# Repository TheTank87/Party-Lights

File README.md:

# Tropical-Fruit-Bowl

# Description
A custom designed PCB that can track humidity, temperature, air pressure, and air quality in ppm. It also includes a gyrscope sensor. This project was heavily inspired by the Starbie and MIDI keyboard projects I did previously, and I wanted to combine them with some new components to see what I can make. This was a pretty exciting experience for me, because for once, I'm not following a guide anymore, and with the lessons and techniques I learned from the previous projects it's like building with LEGO. Once something becomes as fluent as LEGO building, I can let creativity take over.

# Features
* DHT11 Sensor
* MPU6050 gyro Sensor
* The new ENS160+AHT21 air quality sensor
* 2 low profile switches
* Potentiometer
* Rotary Encoder
* OLED

# BOM
| Item | Qty | Supplier | Cost/item | Total Cost | Link |
| --- | --- | --- | --- | --- | --- |
| 0.96 OLED | 1 | AliExpress | $4.38 | $4.38 | [Link](https://www.aliexpress.us/item/3256807427834365.html?src=google&src=google&albch=shopping&acnt=708-803-3821&isdl=y&slnk=&plac=&mtctp=&albbt=Google_7_shopping&aff_platform=google&aff_short_key=UneMJZVf&gclsrc=aw.ds&albagn=888888&ds_e_adid=&ds_e_matchtype=&ds_e_device=c&ds_e_network=x&ds_e_product_group_id=&ds_e_product_id=en3256807427834365&ds_e_product_merchant_id=5851713403&ds_e_product_country=US&ds_e_product_language=en&ds_e_product_channel=online&ds_e_product_store_id=&ds_url_v=2&albcp=19558607238&albag=&isSmbAutoCall=false&needSmbHouyi=false&gad_source=1&gad_campaignid=19566915268&gbraid=0AAAAAD6I-hF0RrES3rCrnIAsdOo0cNEg4&gclid=CjwKCAjwgJHXBhBGEiwAHohJq2PYiClm1aQFLBmOjzYlRhPSXxUHV9mpKWaNqAwxIaVBFqhxzUMuvRoCA2EQAvD_BwE&gatewayAdapt=glo2usa) |
| XIAO ESP32 C3 | 1 | Seeed Studio | $5.20 | $5.20 | [Link](https://www.seeedstudio.com/Seeed-XIAO-ESP32C3-p-5431.html) |
| MPU6050 | 1 | AliExpress | $3.00 | $3.00 | [Link](https://www.aliexpress.us/item/3256809482368154.html?src=google&snps=y&src=google&albch=shopping&acnt=708-803-3821&isdl=y&slnk=&plac=&mtctp=&albbt=Google_7_shopping&aff_platform=google&aff_short_key=UneMJZVf&gclsrc=aw.ds&albagn=888888&ds_e_adid=&ds_e_matchtype=&ds_e_device=c&ds_e_network=x&ds_e_product_group_id=&ds_e_product_id=en3256809482368154&ds_e_product_merchant_id=5851713403&ds_e_product_country=US&ds_e_product_language=en&ds_e_product_channel=online&ds_e_product_store_id=&ds_url_v=2&albcp=20542171667&albag=&isSmbAutoCall=false&needSmbHouyi=false&gad_source=1&gad_campaignid=18545443176&gbraid=0AAAAAD6I-hErqWWSEX2Slh2y8pGIo6r2n&gclid=Cj0KCQjw3YvXBhCDARIsAKB-ox_KDuVSshBCz_K8RTrfuol9tEvBqBcexhKj2D55FBoqYUsrFDhMWooaApfNEALw_wcB&gatewayAdapt=glo2usa) |
| DHT11 | 1 | AliExpress | $1.50 | $1.50 | [Link](https://www.aliexpress.us/item/3256808886855570.html?src=google&src=google&albch=shopping&acnt=708-803-3821&isdl=y&slnk=&plac=&mtctp=&albbt=Google_7_shopping&aff_platform=google&aff_short_key=UneMJZVf&gclsrc=aw.ds&albagn=888888&ds_e_adid=&ds_e_matchtype=&ds_e_device=c&ds_e_network=x&ds_e_product_group_id=&ds_e_product_id=en3256808886855570&ds_e_product_merchant_id=5851713403&ds_e_product_country=US&ds_e_product_language=en&ds_e_product_channel=online&ds_e_product_store_id=&ds_url_v=2&albcp=19558607238&albag=&isSmbAutoCall=false&needSmbHouyi=false&gad_source=1&gad_campaignid=19566915268&gbraid=0AAAAAD6I-hE3WxPZf8MIZjkbVNGkJNmog&gclid=Cj0KCQjw3YvXBhCDARIsAKB-ox_MIsLneSffZbkndQzzN2gGEmgWqn-IT0Po6Tv44LnMdjS0oC_BHe0aAvhYEALw_wcB&gatewayAdapt=glo2usa) |
| Kailh Choc Low-Profile Switches | 2 | AliExpress | $1.50 | $3.00 | [Link](https://www.aliexpress.us/item/3256808697103313.html?spm=a2g0o.productlist.main.1.13d14a7e068OmL&algo_pvid=4e5fe6cd-3562-4ef4-ac3e-085a2d4634fe&algo_exp_id=4e5fe6cd-3562-4ef4-ac3e-085a2d4634fe-0&pdp_ext_f=%7B%22order%22%3A%221475%22%2C%22spu_best_type%22%3A%22price%22%2C%22eval%22%3A%221%22%2C%22fromPage%22%3A%22search%22%7D&pdp_npi=6%40dis%21CAD%2111.40%212.38%21%21%217.81%211.63%21%402103128917919263557114360e0ebd%2112000047082945007%21sea%21CA%210%21ABX%211%210%21n_tag%3A-29910%3Bd%3A778dde27%3Bm03_new_user%3A-29895%3BpisId%3A5000000218640848&curPageLogUid=CXjsh9TOCyFt&utparam-url=scene%3Asearch%7Cquery_from%3A%7Cx_object_id%3A1005008883418065%7C_p_origin_prod%3A&gatewayAdapt=glo2usa4itemAdapt) |
| RotaryEncoder_Alps_EC11E-Switch_Vertical_H20mm | 1 | AliExpress | $1.60 | $1.60 | [Link](https://www.aliexpress.us/item/3256807457768762.html?spm=a2g0o.productlist.main.1.52d22c6as0ZCnv&algo_pvid=9965a6c7-9d4c-44f9-a2d4-a43aa1b0ae45&algo_exp_id=9965a6c7-9d4c-44f9-a2d4-a43aa1b0ae45-0&pdp_ext_f=%7B%22order%22%3A%224739%22%2C%22eval%22%3A%221%22%2C%22fromPage%22%3A%22search%22%7D&pdp_npi=6%40dis%21USD%211.52%211.40%21%21%211.52%211.40%21%402101e7a317919489056767943e0e88%2112000041630839409%21sea%21US%213725344934%21X%211%210%21n_tag%3A-29919%3Bd%3A1bb91aa6%3Bm03_new_user%3A-29895%3BpisId%3A5000000219770668&curPageLogUid=AOe3dpbqRVrY&utparam-url=scene%3Asearch%7Cquery_from%3A%7Cx_object_id%3A1005007644083514%7C_p_origin_prod%3A) |
| ENS160+AHT21 module | 1 | AliExpress | $4.10 | $4.10 | [Link](https://www.aliexpress.us/item/3256812532450753.html?src=google&src=google&albch=shopping&acnt=708-803-3821&isdl=y&slnk=&plac=&mtctp=&albbt=Google_7_shopping&aff_platform=google&aff_short_key=UneMJZVf&gclsrc=aw.ds&albagn=888888&ds_e_adid=&ds_e_matchtype=&ds_e_device=c&ds_e_network=x&ds_e_product_group_id=&ds_e_product_id=en3256812532450753&ds_e_product_merchant_id=5851713403&ds_e_product_country=US&ds_e_product_language=en&ds_e_product_channel=online&ds_e_product_store_id=&ds_url_v=2&albcp=19558607238&albag=&isSmbAutoCall=false&needSmbHouyi=false&gad_source=1&gad_campaignid=19566915268&gbraid=0AAAAAD6I-hE3WxPZf8MIZjkbVNGkJNmog&gclid=Cj0KCQjw3YvXBhCDARIsAKB-ox_0ZPK7KkAejpDl94aN83L3UZbFFqTooBbtk7go9Ezc6xkZ9xmlFmQaAojEEALw_wcB&gatewayAdapt=glo2usa) |
| Potentiometer_Bourns_PTA1543_Single_Slide | 1 | Mouser | $2.25 | $2.25 | [Link](https://www.mouser.com/en/ProductDetail/Bourns/PTA1543-2015CIA103?qs=%252B9%2Fcbd0IE0QZ1Dob%2FcnIYA%3D%3D) |
| SMD Capacitator | 1 | Digikey | $0.13 | $0.13 | [Link](https://www.digikey.com/en/products/detail/yageo/CC0603ZPY5V8BB104/1866826) |
| Axial Resistor | 1 | Digikey | $0.11 | $0.11 | [Link](https://www.digikey.com/en/products/detail/te-connectivity-passive-product/LR0204F10K/2381045) |
| PCB | 1 | JLCPCB | $6.90 | $6.90 | [Link](https://cart.jlcpcb.com/quote?stencilLayer=2&stencilWidth=100&stencilLength=100&stencilCounts=5&plateType=1&spm=Jlcpcb.Homepage.1010) |
| Estimated total shipping | 1 | N/A | $0.00 | $0.00 | N/A |
| **Grand Total** | | | | **$32.17** | |

# Cad Modeling

The cad part was by far the most fun part of this project. I first had to list out what components I want to use because that's really important. Then I have to track down the correct symbols and footprints and sometimes sensors just need a pinheader connection to work. Wiring was pretty easy once I studied what power sources are mandatory and where data should go. I then added a ceramic capacitator to ease electrical noise since my board will be handling lots of data in real time. Bringing the board over to the PCB section I quickly designed the shape and I oriented and wired everything up pretty smoothly. It's like building with LEGO Technics.

# Firmware

## Description
The **Tropical Fruit Bowl** firmware is a an app built on Ardunion C++ designed to showcase the sensors. It features Starbie-like mechanics but the UI is really different. That is because it includes 3 interactive windows for data viewing. I spent the most time designing the firmware and you can see how it should work with the mermaid diagram below. I also decided to add a dedicated section for color customization just in case anyone wants to use this project for themselves. 

## Features
* Moves the cursor, inspired from Starbie, and highlights where your cursor is.
* Intro screen
* Dynamic datas.
* Components adjusts graphs to view liking.
* Asks if you want to exit, instead of just turning off instantly.

## Firmware Flow Chart

## Hardware Controls

| Hardware Component | Pin/Interface | Function in Firmware |
| :--- | :--- | :--- |
| **Switch 1 (SW1)** | `D8` | **Power / Menu**|
| **Switch 2 (SW2)** | `D7` | **Select**|
| **MPU6050 IMU** | `I2C` | **Cursor Movement**|
| **Slide Potentiometer (RV1)** | `D3 (Analog)` | **Y-Axis Graph Control**|
| **Rotary Encoder (SW3)** | `D1 / D2` | **X-Axis Graph Control**|

### Assembly
Assembling this really shouldn't be a problem because I designed the pcb so that all components will have space inbetween other components, so one shouldn't worry about overlapping components. The sensors especiallu the gyroscope an air quality sensors should come with pin headers in the package so I wouldn't buy generic pin heads seperately.

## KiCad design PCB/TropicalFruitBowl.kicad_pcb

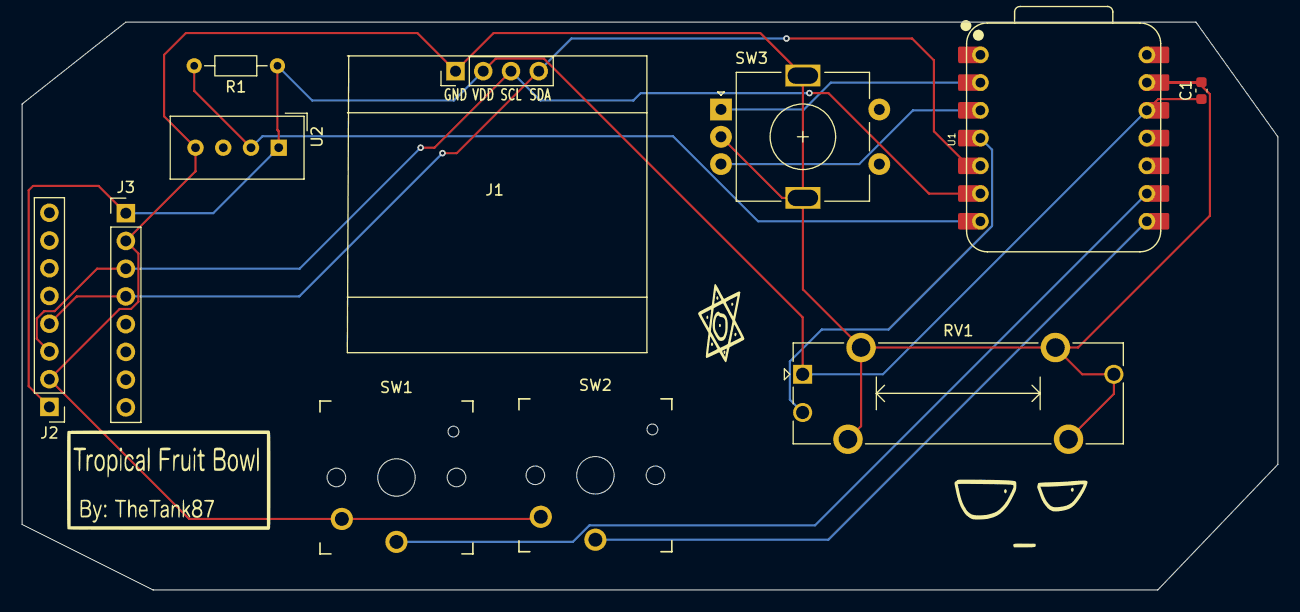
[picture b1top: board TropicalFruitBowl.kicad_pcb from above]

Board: 2 copper layers, 115.0 x 52.0 mm, 11 parts (0 on the bottom side), 10 nets.

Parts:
C1: 0.1uF; C_0603_1608Metric
J1: OLED; Display_128x64_096_I2C
J2: ENS160+AHT21 module; PinHeader_1x08_P2.54mm_Vertical
J3: MPU6050; PinHeader_1x08_P2.54mm_Vertical
R1: 10K; R_Axial_DIN0204_L3.6mm_D1.6mm_P7.62mm_Horizontal
RV1: Slider; Potentiometer_Bourns_PTA1543_Single_Slide
SW1, SW2: SW_Push; Kailh Choc Low-Profile Switches
SW3: RotaryEncoder_Switch_MP; RotaryEncoder_Alps_EC11E-Switch_Vertical_H20mm
U1: XIAO-ESP32-C3-SMD; XIAO-ESP32-C6-DIP
U2: DHT11; Aosong_DHT11_5.5x12.0_P2.54mm

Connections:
+3V3: C1.1, J1.2, J2.1, J3.1, R1.1, RV1.1, U1.12 (3V3_OUT), U2.1 (VDD)
/DATA: R1.2, U1.7 (D6), U2.2 (DATA)
/ENC1: SW3.A, U1.2 (D1)
/ENC2: SW3.B, U1.3 (D2)
/GPIO1: SW1.1, U1.9 (D8)
/GPIO2: SW2.1, U1.8 (D7)
/SCL: J1.3, J2.3, J3.3, U1.6 (D5)
/SDA: J1.4, J2.4, J3.4, U1.5 (D4)
/Slide: RV1.2, U1.4 (D3)
GND: C1.2, J1.1, J2.2, J3.2, RV1.3, RV1.MP (MountPin), SW1.2, SW2.2, SW3.C, SW3.MP, U1.13 (GND), U2.4 (GND)

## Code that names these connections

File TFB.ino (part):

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// ============================================================================
// Hardware Pin Defs 
// ============================================================================
#define PIN_ENC1    D1   // ENC1
#define PIN_ENC2    D2   // ENC2
#define PIN_SLIDER  D3   // Slide
#define PIN_I2C_SDA D4   // SDA
#define PIN_I2C_SCL D5   // SCL
#define PIN_DHT     D6   // DATA
#define PIN_SW2     D7   // GPIO2
#define PIN_SW1     D8   // GPIO1 

// ============================================================================
// Display and Color customization settings
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volatile int lastEncoded = 0;

void IRAM_ATTR updateRotaryEncoder() {
  int MSB = digitalRead(PIN_ENC1);
  int LSB = digitalRead(PIN_ENC2);

  int encoded = (MSB << 1) | LSB;
  int sum = (lastEncoded << 2) | encoded;
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  
  pinMode(PIN_SW1, INPUT_PULLUP);
  pinMode(PIN_SW2, INPUT_PULLUP);
  pinMode(PIN_ENC1, INPUT_PULLUP);
  pinMode(PIN_ENC2, INPUT_PULLUP);
  pinMode(PIN_SLIDER, INPUT);

  
  attachInterrupt(digitalPinToInterrupt(PIN_ENC1), updateRotaryEncoder, CHANGE);
  attachInterrupt(digitalPinToInterrupt(PIN_ENC2), updateRotaryEncoder, CHANGE);

  // Initialize I2C Bus on XIAO D4
  Wire.begin(PIN_I2C_SDA, PIN_I2C_SCL);
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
